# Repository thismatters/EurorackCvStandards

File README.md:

# Control Voltage Standards

The Control Voltage Standards is a module for providing precise voltages. This module is enabled by a whole bunch of potentiometers.

The circuit here is based on the [CV Standards](https://yusynth.net/Modular/EN/STANDARDS/index.html) with minor tweaks to make it more Eurorack friendly. The changes I've made are thus:
* Selected resistors appropriate for +/-12V rails,
* Added polarity protection so that a backward power header doesn't fry anything (twin series schotty diodes: BAT54SL),
* Full surface mount design.

The Yusynth page is a treasure trove of information about this circuit that I am too amateur to claim as my own; please read that outstanding page before using this circuit. The page provides many details and other implementations of this circuit that you may find suitable.

The KiCAD project here uses the library/footprints [found in my companion repo](https://github.com/thismatters/EurorackKiCAD).

## Width

4hp on a standard 3U rack.

## Inputs

Twin 12 position switches which allow selection of `octave` and `semitone`. A jack allows input of control voltage to offset the selected tone.

## Outputs

Three buffered jacks output control voltage.

## Adjustment

Oh boy. TODO

## Vendors

There are part numbers in the [BOM](cv-standard.csv) for many of the parts (not for basic passives though) at the following vendors:

* [Mouser](https://www.mouser.com): Needs no introduction. Get your ICs from here (or [digikey](https://www.digikey.com)).
* [Tayda Electronics](https://www.taydaelectronics.com/): Good supplier for passive components; audio jacks, and potentiometers. Their audio jacks are slightly smaller than the thonkiconn from thonk.
* [Love My Switches](https://lovemyswitches.com/): Has [really good knobs](https://lovemyswitches.com/anodized-aluminum-knob-the-lo-fi-1-4-smooth-shaft-12-5mm-od/) to go on those potentiometers!
* [OSHPark](https://oshpark.com/): Fast and (relatively) cheap PCB manufacturer. I haven't done a prototype run yet... stay tuned.

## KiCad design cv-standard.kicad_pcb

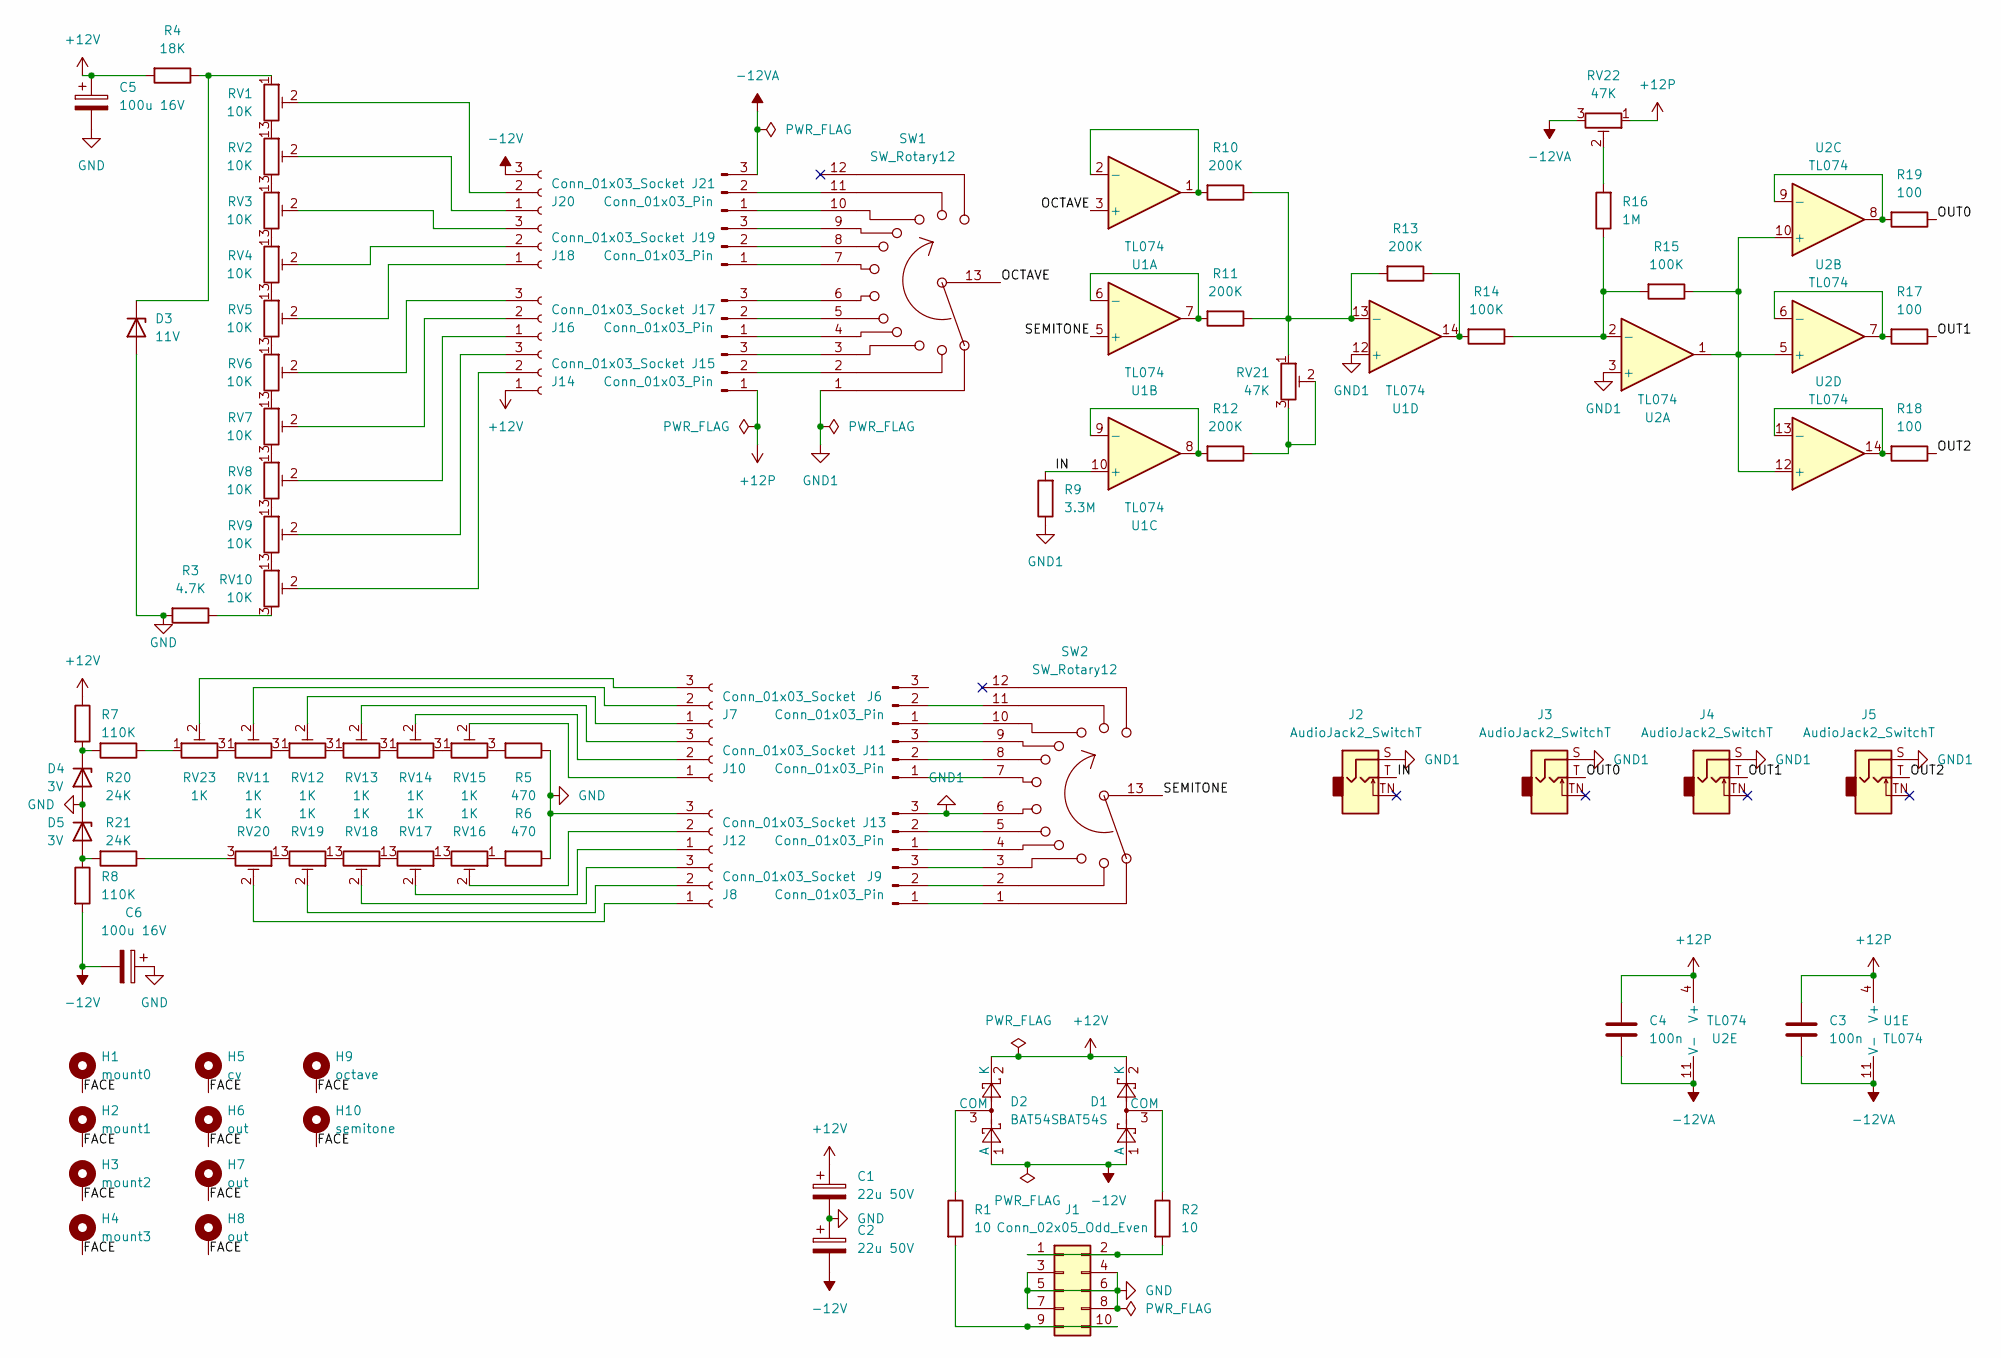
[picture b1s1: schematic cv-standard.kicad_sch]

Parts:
C1, C2: 22u 50V; CP_Radial_D5.0mm_P2.50mm
C3, C4: 100n; C_0805_2012Metric
C5, C6: 100u 16V; CP_Radial_D5.0mm_P2.50mm
D1, D2: BAT54S; SOT-23; PartNum 863-BAT54SLT1G
D3: 11V; D_MiniMELF
D4, D5: 3V; D_MiniMELF
H1: mount0; Mech-MountingHole
H2: mount1; Mech-MountingHole
H3: mount2; Mech-MountingHole
H4: mount3; Mech-MountingHole
H5: cv; Mech-AudioJack-Hole-Input-Voct
H6, H7, H8: out; Mech-AudioJack-Hole-Output-Voct
H9: octave; Mech-MRK-Hole
H10: semitone; Mech-MRK-Hole
J1: Conn_02x05_Odd_Even; PinHeader_2x05_P2.54mm_Vertical; PartNum A-2939
J2, J3, J4, J5: AudioJack2_SwitchT; AudioJack2_Tayda_A-2566; PartNum A-2566
J6, J9, J11, J13, J15, J17, J19, J21: Conn_01x03_Pin; PinHeader_1x03_P2.54mm_Vertical
J7, J8, J10, J12, J14, J16, J18, J20: Conn_01x03_Socket; PinSocket_1x03_P2.54mm_Vertical
R1, R2: 10; R_0805_2012Metric
R3: 4.7K; R_0805_2012Metric
R4: 18K; R_0805_2012Metric
R5, R6: 470; R_0805_2012Metric
R7, R8: 110K; R_0805_2012Metric
R9: 3.3M; R_0805_2012Metric
R10, R11, R12, R13: 200K; R_0805_2012Metric
R14, R15: 100K; R_0805_2012Metric
R16: 1M; R_0805_2012Metric
R17, R18, R19: 100; R_0805_2012Metric
R20, R21: 24K; R_0805_2012Metric
RV1, RV2, RV3, RV4, RV5, RV6, RV7, RV8, RV9, RV10: 10K; Potentiometer_Bourns_3296W_Vertical
RV11, RV12, RV13, RV14, RV15, RV16, RV17, RV18, RV19, RV20, RV23: 1K; Potentiometer_Bourns_3296W_Vertical
RV21, RV22: 47K; Potentiometer_Bourns_3296W_Vertical
SW1, SW2: SW_Rotary12; Switch_Rotary_NKK_MRK_112; PartNum 633-MRK112-BA
U1, U2: TL074; SOIC-14_3.9x8.7mm_P1.27mm; PartNum 595-TL074CDR

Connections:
+12P: C3.1, C4.1, J15.1, RV22.1, U1.4 (V+), U2.4 (V+)
+12V: C1.1, C5.1, D1.2 (K), D2.2 (K), J14.1, R4.2, R7.1
-12V: C2.2, C6.2, D1.1 (A), D2.1 (A), J20.3, R8.2
-12VA: C3.2, C4.2, J21.3, RV22.3, U1.11 (V-), U2.11 (V-)
/FACE: H1.1, H2.1, H3.1, H4.1, H5.1, H6.1, H7.1, H8.1, H9.1, H10.1
/IN: J2.T, R9.2, U1.10 (+)
/OCTAVE: SW1.13, U1.3 (+)
/OUT0: J3.T, R19.1
/OUT1: J4.T, R17.1
/OUT2: J5.T, R18.1
/SEMITONE: SW2.13, U1.5 (+)
GND: C1.2, C2.1, C5.2, C6.1, D3.2 (A), D4.2 (A), D5.1 (K), J1.3, J1.4, J1.5, J1.6, J1.7, J1.8, J12.3, R3.2, R5.1, R6.1
GND1: J2.S, J3.S, J4.S, J5.S, J13.3, R9.1, SW1.1, SW2.6, U1.12 (+), U2.3 (+)
unnamed: D1.3 (COM), R2.1
unnamed: D2.3 (COM), R1.1
unnamed: D3.1 (K), R4.1, RV1.1
unnamed: D4.1 (K), R7.2, R20.2
unnamed: D5.2 (A), R8.1, R21.2
unnamed: J1.1, J1.2, R2.2
unnamed: J1.9, J1.10, R1.2
unnamed: J6.1, SW2.10
unnamed: J6.2, SW2.11
unnamed: J7.1, RV12.2
unnamed: J7.2, RV11.2
unnamed: J7.3, RV23.2
unnamed: J8.1, RV20.2
unnamed: J8.2, RV19.2
unnamed: J8.3, RV18.2
unnamed: J9.1, SW2.1
unnamed: J9.2, SW2.2
unnamed: J9.3, SW2.3
unnamed: J10.1, RV15.2
unnamed: J10.2, RV14.2
unnamed: J10.3, RV13.2
unnamed: J11.1, SW2.7
unnamed: J11.2, SW2.8
unnamed: J11.3, SW2.9
unnamed: J12.1, RV17.2
unnamed: J12.2, RV16.2
unnamed: J13.1, SW2.4
unnamed: J13.2, SW2.5
unnamed: J14.2, RV10.2
unnamed: J14.3, RV9.2
unnamed: J15.2, SW1.2
unnamed: J15.3, SW1.3
unnamed: J16.1, RV8.2
unnamed: J16.2, RV7.2
unnamed: J16.3, RV6.2
unnamed: J17.1, SW1.4
unnamed: J17.2, SW1.5
unnamed: J17.3, SW1.6
unnamed: J18.1, RV5.2
unnamed: J18.2, RV4.2
unnamed: J18.3, RV3.2
unnamed: J19.1, SW1.7
unnamed: J19.2, SW1.8
unnamed: J19.3, SW1.9
unnamed: J20.1, RV2.2
unnamed: J20.2, RV1.2
unnamed: J21.1, SW1.10
unnamed: J21.2, SW1.11
unnamed: R3.1, RV10.3
unnamed: R5.2, RV15.3
unnamed: R6.2, RV16.1
unnamed: R12.1, RV21.2, RV21.3
unnamed: R13.1, R14.2, U1.14
unnamed: R16.2, RV22.2
unnamed: R20.1, RV23.1
unnamed: R21.1, RV20.3
unnamed: RV1.3, RV2.1
unnamed: RV2.3, RV3.1
unnamed: RV3.3, RV4.1
unnamed: RV4.3, RV5.1
unnamed: RV5.3, RV6.1
unnamed: RV6.3, RV7.1
unnamed: RV7.3, RV8.1
unnamed: RV8.3, RV9.1
unnamed: RV9.3, RV10.1
unnamed: RV11.1, RV23.3
unnamed: RV11.3, RV12.1
unnamed: RV12.3, RV13.1
unnamed: RV13.3, RV14.1
unnamed: RV14.3, RV15.1
unnamed: RV16.3, RV17.1
unnamed: RV17.3, RV18.1
unnamed: RV18.3, RV19.1
unnamed: RV19.3, RV20.1
unnamed: R10.2, U1.1, U1.2 (-)
unnamed: R11.2, U1.6 (-), U1.7
unnamed: R12.2, U1.8, U1.9 (-)
unnamed: R10.1, R11.1, R13.2, RV21.1, U1.13 (-)
unnamed: R14.1, R15.2, R16.1, U2.2 (-)
unnamed: R15.1, U2.1, U2.5 (+), U2.10 (+), U2.12 (+)
unnamed: R17.2, U2.6 (-), U2.7
unnamed: R19.2, U2.8, U2.9 (-)
unnamed: R18.2, U2.13 (-), U2.14

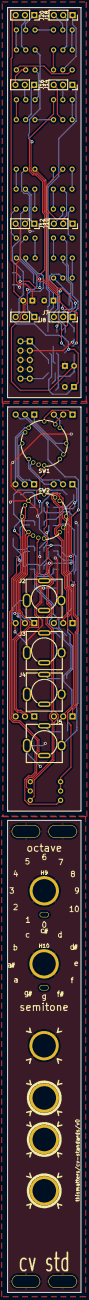
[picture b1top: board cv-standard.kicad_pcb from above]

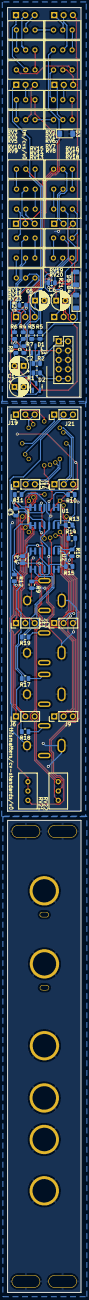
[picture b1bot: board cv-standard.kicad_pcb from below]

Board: 2 copper layers, 20.0 x 349.8 mm, 90 parts (66 on the bottom side), 96 nets.
